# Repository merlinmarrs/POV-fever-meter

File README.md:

# POV-fever-meter

Developed by Fablab Digiscope

This device is based on the the MLX90614 IR temperature sensor. It uses 5 LEDs to display the temperature exploiting the POV phenomenon. It's powered with a 3V CR2032 coin cell battery and is programmable with ISP.

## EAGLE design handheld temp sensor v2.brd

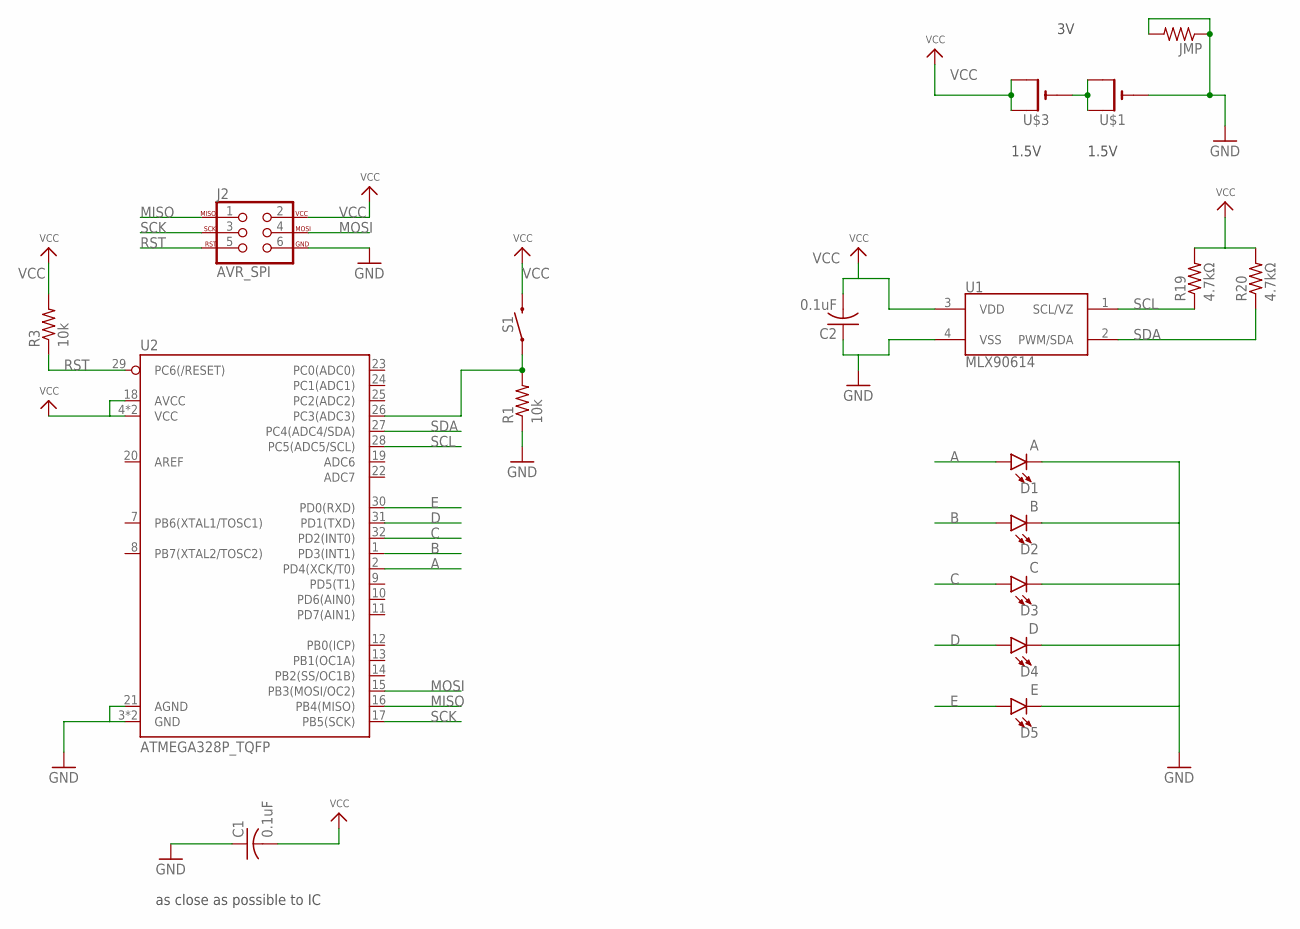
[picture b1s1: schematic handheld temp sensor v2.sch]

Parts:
C1, C2: 0.1uF; C1206
D1: A; LED-1206
D2: B; LED-1206
D3: C; LED-1206
D4: D; LED-1206
D5: E; LED-1206
J2: AVR_SPI; 2X3_SMT_POSTS
JMP: R-US_R1206; R1206
R1, R3: 10k; R1206
R19, R20: 4.7kΩ; R1206
S1: MOMENTARY-SWITCH-SPST-PTH-6.0MM; TACTILE_SWITCH_PTH_6.0MM
U1: MLX90614; TO-39
U2: ATMEGA328P_TQFP; TQFP32-08
U$1, U$3: CR1220THM; CR1220-THM

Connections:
A: D1.A, U2.2 (PD4(XCK/T0))
B: D2.A, U2.1 (PD3(INT1))
C: D3.A, U2.32 (PD2(INT0))
D: D4.A, U2.31 (PD1(TXD))
E: D5.A, U2.30 (PD0(RXD))
GND: C1.1, C2.1, D1.C, D2.C, D3.C, D4.C, D5.C, J2.6, JMP.1, JMP.2, R1.1, U1.4 (VSS), U2.3 (GND), U2.5 (GND), U2.21 (AGND), U$1.-
MISO: J2.1, U2.16 (PB4(MISO))
MOSI: J2.4, U2.15 (PB3(MOSI/OC2))
unnamed: R1.2, S1.1, U2.26 (PC3(ADC3))
unnamed: U$1.+1 (+), U$1.+2 (+1), U$3.-
RST: J2.5, R3.1, U2.29 (PC6(/RESET))
SCK: J2.3, U2.17 (PB5(SCK))
SCL: R19.1, U1.1 (SCL/VZ), U2.28 (PC5(ADC5/SCL))
SDA: R20.1, U1.2 (PWM/SDA), U2.27 (PC4(ADC4/SDA))
VCC: C1.2, C2.2, J2.2, R3.2, R19.2, R20.2, S1.3 (2), U1.3 (VDD), U2.4 (VCC), U2.6 (VCC), U2.18 (AVCC), U$3.+1 (+), U$3.+2 (+1)

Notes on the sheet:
as close as possible to IC
1.5V

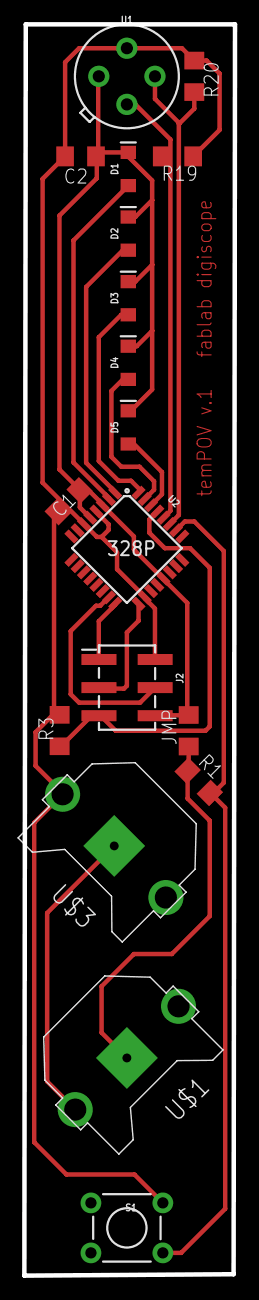
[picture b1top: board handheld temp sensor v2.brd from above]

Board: 2 copper layers, 19.0 x 113.2 mm, 18 parts (0 on the bottom side), 15 nets.

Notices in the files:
parts and their libraries:
SparkFun-IC-Microcontroller: Licensing: Creative Commons ShareAlike 4.0 International - https://creativecommons.org/licenses/by-sa/4.0
